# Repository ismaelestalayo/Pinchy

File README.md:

# Pinchy

[Pinchy](http://bilbaodynamics.com/pinchy) is presented as the second iteration of our previous robot, [uBot](http://bilbaodynamics.com/tenacitas). It is an **educational** robot specifically made to be used as an ideal medium to start learning to program, know more about robotics and familiarize yourself with the basic electronic concepts.

### What's this?

Pinchy is an **open source** educational robot that can be printed using ordinary 3D printers. It's made up of a PCB, used as a shield with an Arduino Micro on top of it, the before mentioned chasis and some sensors to interact.

| **Unidades** 	|        **Componente**       	|
|:------------:	|:---------------------------:	|
|       2      	| Continuous Rotation Servos 	|
|       1      	|         Ultrasound Sensor        	|
|       2      	|     Line Follower Sensor    	|
|       1      	|           RGB LED           	|
|       1      	|            Buzzer           	|
|       1      	|       Bluetooth Module      	|
|       1      	|          Protoboard         	|
|       1       |       5x7 LED Array      |
|       1       |        Arduino Micro          |

## I/O Ports

| **Pin** | **Function** |
|:-------:|:---------------------------:|
| 0 | TX / BT Module |
| 1 | RX / BT Module |
| 2 | Buzzer |
| 3 | Free I/O / Pincer Servo |
| 4 | Optorreflector 1 |
| 5 | Servomotor 1 |
| 6 | Servomotor 2 |
| 7 | Trigger Ultrasound Sensor |
| 8 | Echo Ultrasound Sensor |
| 9 | Blue RGB LED |
| 10 | Red RGB LED |
| 11 | Green RGB LED |
| 12 | Optorreflector 2 |
| 13 | Free I/O |
| 14 | Push Switch |
| 15 | MAX7219 SCK |
| 16 | MAX7219 MOSI |
| 17 | MAX7219 SS |
| A0 | Free I/O |
| A1 | Free I/O |
| A2 | Free I/O |
| A3 | Free I/O |
| A4 | Free I/O |
| A5 | Free I/O |
| A6 | Free I/O |
| A7 | Free I/O |

## Files

### Chasis

The chasis that makes this robot more than a custom PCB with an Arduino is made with our 3D printers helping us to reduce the costs of assembling a fully functional educational robot. All the necessary files are [here](https://github.com/BilbaoDynamics/Pinchy/tree/master/Chasis).

>
Pinchy's chasis without the circuitry
>

### Circuit and Board

>
Pinchy's main PCB
>

The circuitry that is needed is in the [Circuits](https://github.com/BilbaoDynamics/Pinchy/tree/master/Circuitos) folder, there you can find the schematics and the CAD files for the main PCB and for the custom-made optoreflectors.

## Contributing to this project

If you find a bug in the code or an issue in the circuit, we would like to know it so please follow the next steps so we are aware of it:

1. Fork this repository
2. Create your feature branch: `git checkout -b my-new-feature`
3. Commit your changes: `git commit -am "Hey Bilbao Dynamics, I've added something that you might like!"`
4. Push to the branch: `git push origin my-new-feature`
5. Submit a pull request and we might add it to the project! 😉

## License

GPL license or Creative Commons Attribution-ShareAlike (Copyleft)

## Contact us

We are an active group of students that want to stay in touch if there are some issues or new things that you want to share with us. We are available on the following sites:

* [Twitter](https://twitter.com/BilbaoDynamics)
* [Facebook](https://www.facebook.com/BilbaoDynamics/)
* [Our website](https://www.bilbaodynamics.com)

>
Bilbao Dynamics @ 2016
>

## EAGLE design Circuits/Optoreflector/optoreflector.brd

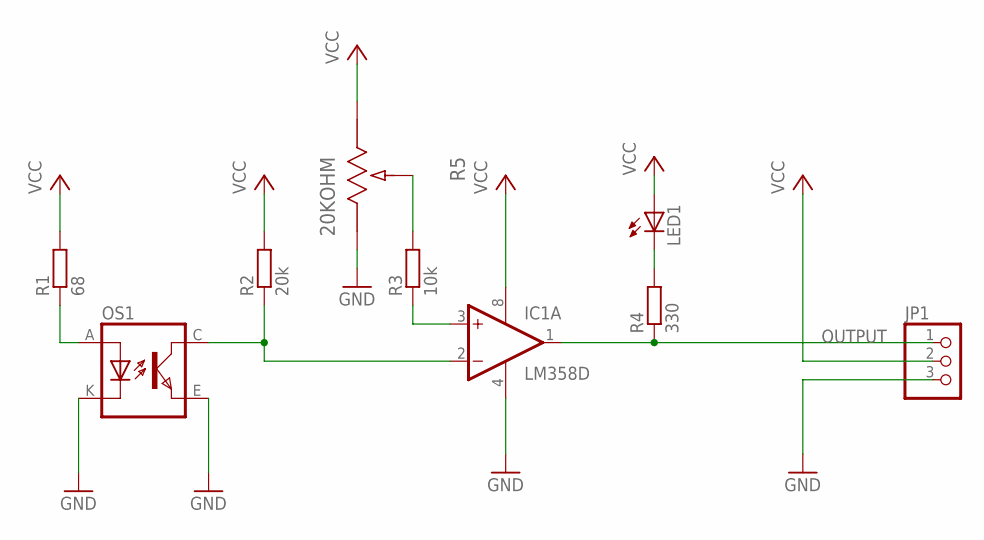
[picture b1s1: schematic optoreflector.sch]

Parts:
IC1: LM358D; SO08
JP1: PINHD-1X3; 1X03
LED1: LEDCHIP-LED0805; CHIP-LED0805
OS1: TCRT5000
R1: 68; R0805
R2: 20k; R0805
R3: 10k; R0805
R4: 330; R0805
R5: 20KOHM; POT_EVM2W

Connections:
GND: IC1.4 (V-), JP1.3, OS1.E (EMITTER), OS1.K (CATHODE), R5.3
unnamed: LED1.C, R4.2
unnamed: OS1.A (ANODE), R1.1
unnamed: IC1.2 (-IN), OS1.C (COLLECTOR), R2.1
unnamed: R3.2, R5.2
unnamed: IC1.3 (+IN), R3.1
OUTPUT: IC1.1 (OUT), JP1.1, R4.1
VCC: IC1.8 (V+), JP1.2, LED1.A, R1.2, R2.2, R5.1

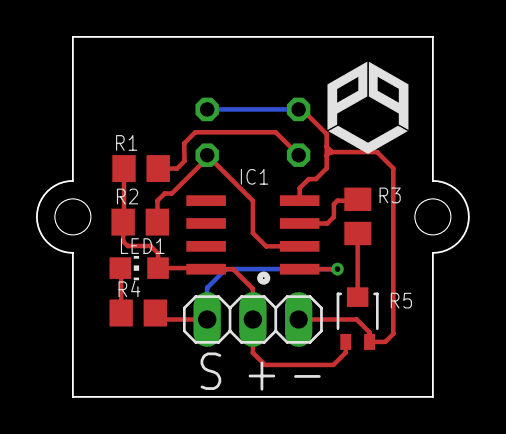
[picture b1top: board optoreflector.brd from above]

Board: 2 copper layers, 24.0 x 20.0 mm, 9 parts (1 on the bottom side), 8 nets.

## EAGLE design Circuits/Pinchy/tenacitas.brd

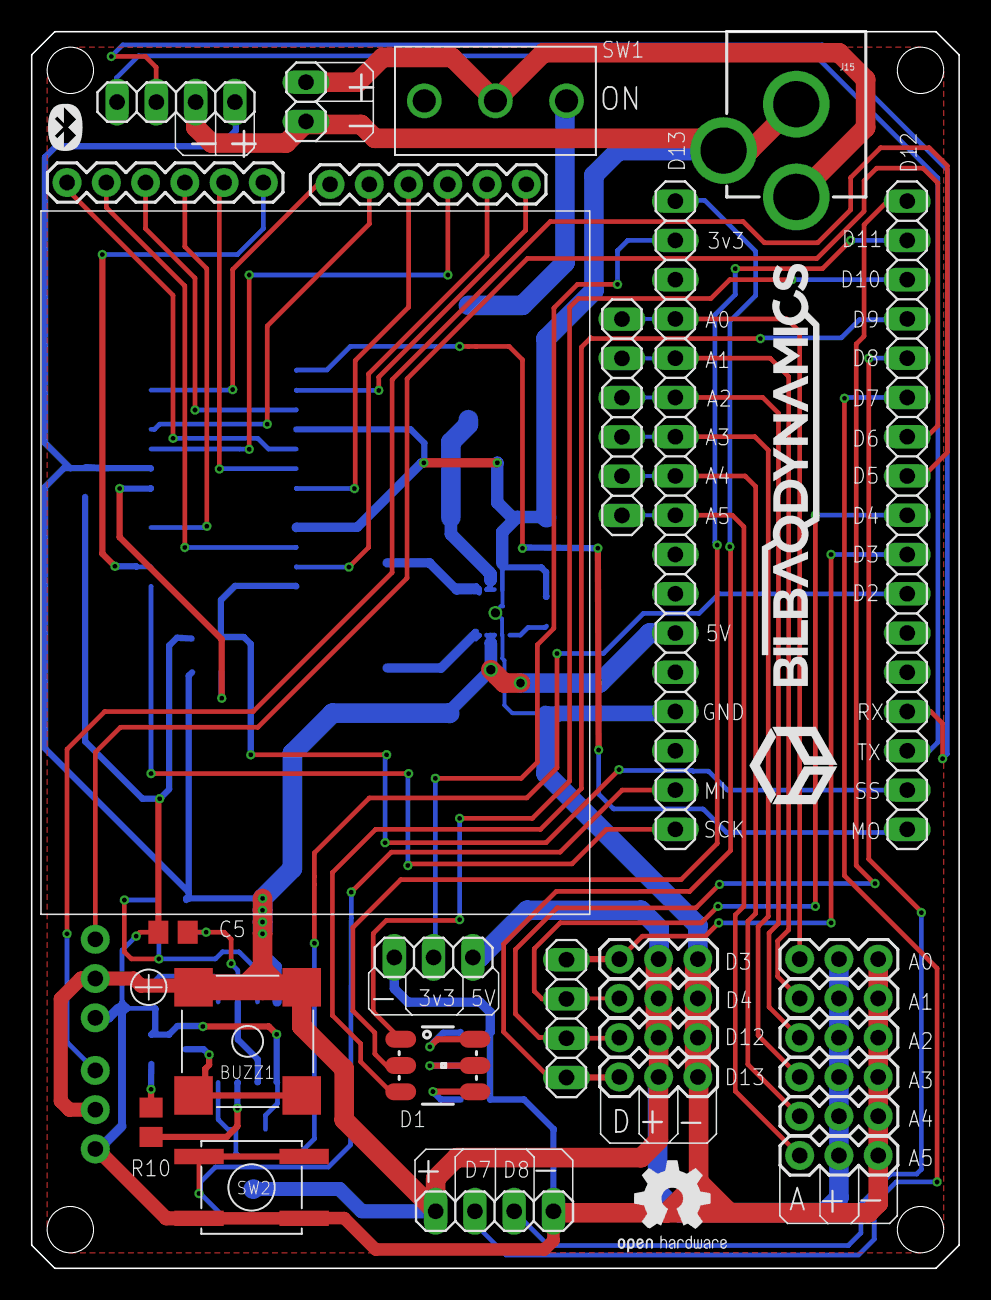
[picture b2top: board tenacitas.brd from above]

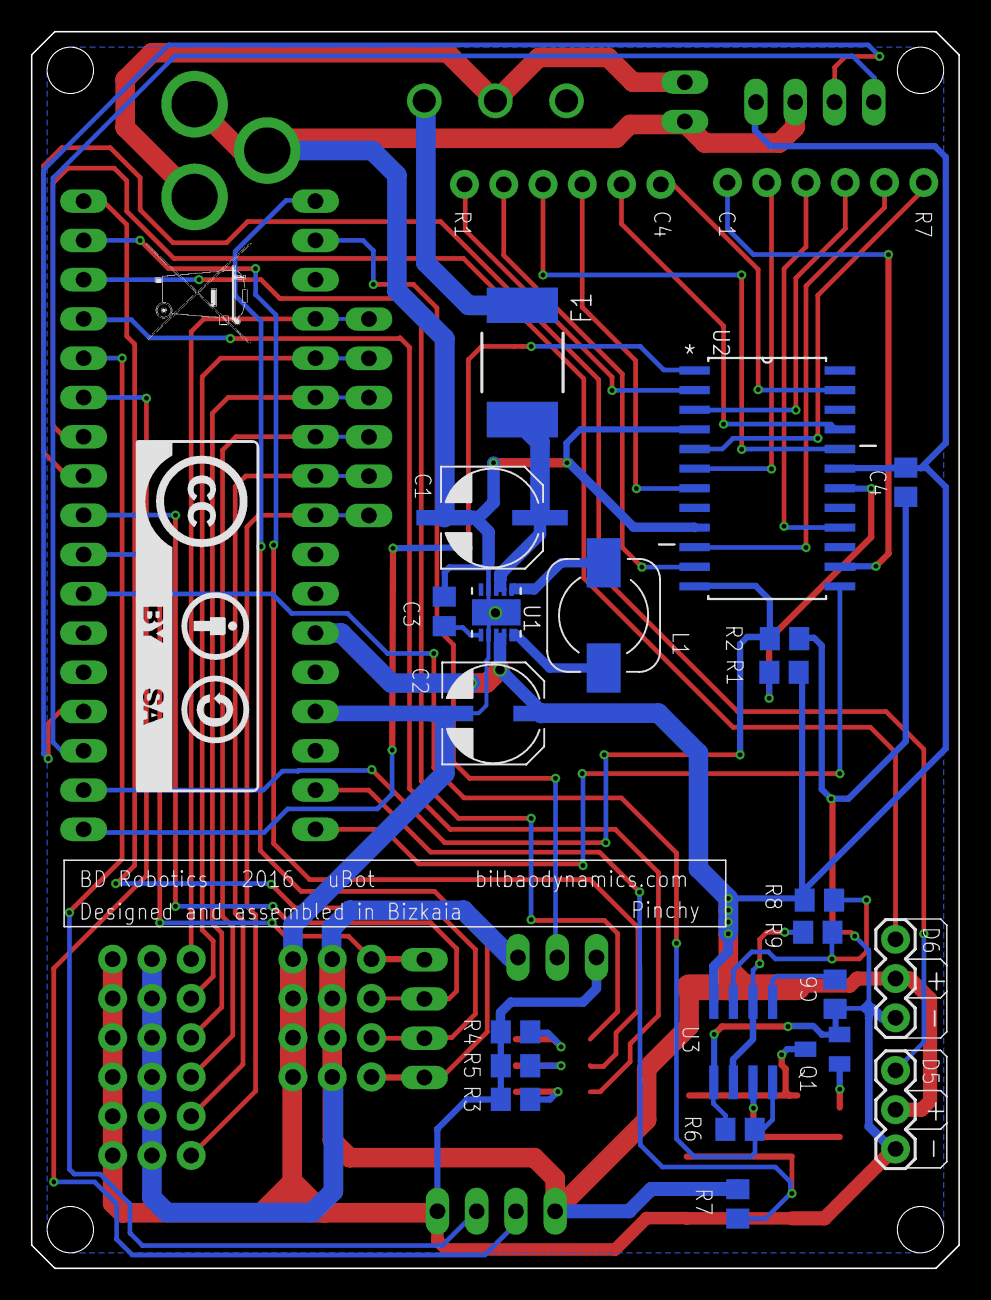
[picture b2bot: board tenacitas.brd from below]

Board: 2 copper layers, 60.0 x 80.0 mm, 49 parts (22 on the bottom side), 55 nets.

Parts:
BUZZ1: KSSG74B16
C1, C2: 100uF; EDK107M016A9G
C3, C4, C6: 0.1uF; C0805
C5: 220nF; C0805
D1: LED-TRICOLOR-5050NO_IC; LED-TRICOLOR-5050
F1: SMD260F; SMD050F
J1: Tenacita; 1X03
J2: OptoreflectorA; 1X03
J3: ServoA; 1X03
J4: ServoB; 1X03
J5: OptoreflectorB; 1X03
J6: D13; 1X03
J7: AN0; 1X03
J8: AN1; 1X03
J9: AN2; 1X03
J10: AN3; 1X03
J11: AN4; 1X03
J12: AN5; 1X03
J13: 1X04
J15: POWER_JACKPTH; POWER_JACK_PTH
J16, J17: 1X06
J19: Utrasonic; 1X04
J20: Analogicas; 1X06
J21: Bluetooth; 1X04
J22: Alimentacion; 1X03
J23, J24: 1X17
J25: 1X02
L1: 1uH; MCSDRH73B
Q1: BC847; SOT23
R1: 62k; R0805
R2, R6, R7: 10k; R0805
R3, R4, R5: 330; R0805
R8: 820; R0805
R9: 750; R0805
R10: 1k; R0805
SW1: MFP106D
SW2: EVQQ2; JAEGGER_MKII_EVQQ2
U1: TPS63061DSCT; SON50P300X300X80-11N
U2: MAX7219CWG+; SOIC127P1032X265-24N
U3: LM555D; SO08

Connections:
3.3V: J22.2, J24.16
+5V: BUZZ1.P$2, BUZZ1.P$3, C2.1, C4.1, J1.2, J2.2, J3.2, J4.2, J5.2, J6.2, J7.2, J8.2, J9.2, J10.2, J11.2, J12.2, J19.1, J21.1, J22.1, J24.6, R1.2, R7.2, R8.2, U1.8, U1.9, U2.19, U3.8
A0: J7.1, J20.6, J24.14
A1: J8.1, J20.5, J24.13
A2: J9.1, J20.4, J24.12
A3: J10.1, J20.3, J24.11
A4: J11.1, J20.2, J24.10
A5: J12.1, J20.1, J24.9
C1: J17.1, U2.14
C2: J17.3, U2.16
C3: J16.3, U2.20
C4: J16.6, U2.23
C5: J16.5, U2.21
D0/RX: J21.3, J23.4
D1/TX: J21.4, J23.3
D2: J23.7, R6.1, U3.4
D3: J1.1, J13.1, J23.8
D4: J2.1, J13.2, J23.9
D5: J3.1, J23.10
D6: J4.1, J23.11
D7: J19.2, J23.12
D8: J19.3, J23.13
D9: D1.3, J23.14
D10: D1.1, J23.15
D11: D1.2, J23.16
D12: J5.1, J13.3, J23.17
D13: J6.1, J13.4, J24.17
D14: J24.2, R7.1, SW2.P$1, SW2.P$4
D15/SCK: J24.1, U2.13
D16/MOSI: J23.1, U2.1
D17/SS: J23.2, R2.2, U2.12
GND: C1.2, C2.2, C3.2, C4.2, C5.2, C6.2, J1.3, J2.3, J3.3, J4.3, J5.3, J6.3, J7.3, J8.3, J9.3, J10.3, J11.3, J12.3, J15.GND, J15.GNDBREAK, J19.4, J21.2, J22.3, J24.4, J25.2, Q1.2, R2.1, R3.1, R4.1, R5.1, R6.2, SW2.P$2, SW2.P$3, U1.4, U1.7, U1.11, U2.4, U2.9, U3.1
unnamed: R8.1, R9.2, U3.7
unnamed: R10.2, U3.3
unnamed: D1.4, R3.2
unnamed: D1.6, R4.2
unnamed: C3.1, U1.6
unnamed: D1.5, R5.2
unnamed: L1.2, U1.1
unnamed: L1.1, U1.10
unnamed: BUZZ1.P$1, BUZZ1.P$4, Q1.3
unnamed: C5.1, R9.1, U3.2, U3.6
unnamed: F1.1, SW1.2
unnamed: C6.1, U3.5
unnamed: Q1.1, R10.1
unnamed: R1.1, U2.18
unnamed: J15.PWR, J25.1, SW1.COM
R1: J16.1, U2.2
R2: J16.2, U2.11
R3: J17.2, U2.6
R4: J16.4, U2.7
R5: J17.4, U2.3
R6: J17.5, U2.10
R7: J17.6, U2.5
VCC: C1.1, F1.2, U1.2, U1.3

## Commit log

2016-03-18 Añadida información al README.md y añadidos los diseños en 3D necesarios para el robot
2016-03-19 Corrección de errores
2016-03-21 Añadida imagen con todos los componentes del chasis y nuevos diseños
2016-03-21 Enlazada imagen del chasis
2016-03-21 Imagen centrada
2016-03-22 Modificado error en los pines del LED RGB
2016-03-26 Incluidos los esquemáticos para Pinchy y el optoreflector
2016-03-27 File translated to english 🇬🇧
2016-03-27 Added two images of the PCBs
2016-03-27 File translated to english 🇬🇧
2016-03-27 Updated Pinchy's PCB image
2016-04-18 Added circuits folder
2016-04-18 Traduction to spanish completed
2016-09-29 Añadir librería matriz
    Librería para la matriz de Pinchy facilitando su programación.
2016-11-15 Added 3 emojis and 1 new function
    Added 3 new icons (equal sign, FB like, and +1)
    and a funtcion to parse a string of binary digits onto the matrix.
2017-03-03 Added examples folder
2017-04-16 Added PinchyBluetooth folder

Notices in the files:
parts and their libraries:
SparkFun-LED: Licensing: Creative Commons ShareAlike 4.0 International - https://creativecommons.org/licenses/by-sa/4.0
